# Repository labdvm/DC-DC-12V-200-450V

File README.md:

# DC-DC-12V-200-450V
DC-DC Buck convertor up to 70W@450V
This is modified DC-DC convertor from chinese product from Aliexpress with little enhancement.
Take out the transformer from original PCB and place to this PCB !
V1.3
Z32IT

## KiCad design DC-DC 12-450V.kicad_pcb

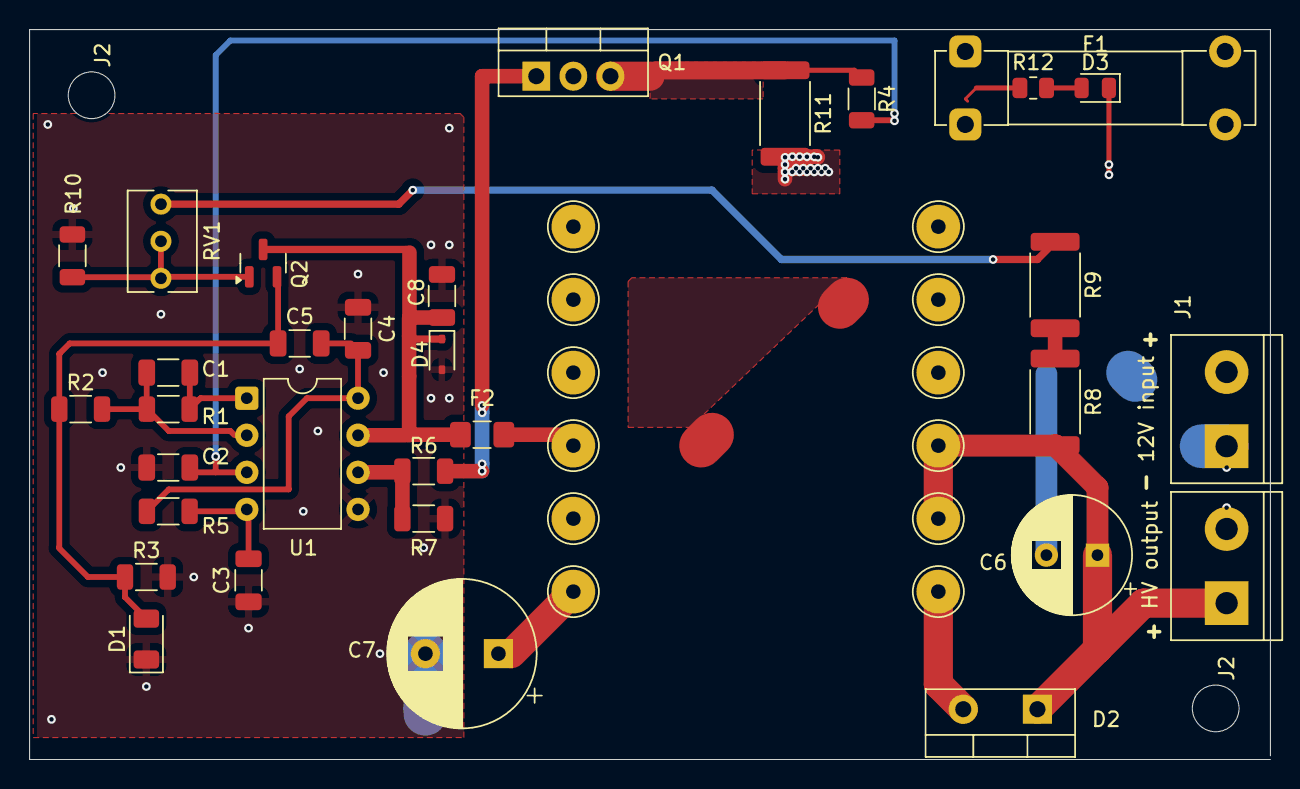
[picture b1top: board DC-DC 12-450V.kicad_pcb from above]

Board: 2 copper layers, 85.0 x 50.0 mm, 44 parts (0 on the bottom side), 19 nets.

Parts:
C1, C8: 100n; C_1206_3216Metric
C2, C4, C5: 10n; C_1206_3216Metric
C3: 3n3; C_1206_3216Metric
C6: 10u/450V; CP_Radial_D8.0mm_P3.50mm
C7: 1500u/16V; CP_Radial_D10.0mm_P5.00mm
D1: Green; LED_1206_3216Metric
D2: MUR860; TO-220-2_Vertical
D3: Amber; LED_0805_2012Metric
D4: PESD12VL1BA; D_SOD-323
F1: Fuse; Fuseholder_Clip-5x20mm_Bel_FC-203-22_Lateral_P17.80x5.00mm_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
F2: 1.5A/13.2V; Fuse_1206_3216Metric_Pad1.42x1.75mm_HandSolder
J1: 12V input; TerminalBlock_bornier-2_P5.08mm
J2: HV output; TerminalBlock_bornier-2_P5.08mm
PAD1, PAD6, PAD7: +12V; TestPoint_THTPad_D3.0mm_Drill1.5mm
PAD2, PAD3, PAD5, PAD8, PAD10, PAD11: e; TestPoint_THTPad_D3.0mm_Drill1.5mm
PAD4, PAD9: TestPoint_THTPad_D3.0mm_Drill1.5mm
PAD12: Q1-D; TestPoint_THTPad_D3.0mm_Drill1.5mm
Q1: IRF3205; TO-220-3_Vertical
Q2: S8050; SOT-23
R1: 100K; R_1206_3216Metric
R2, R3: 1K; R_1206_3216Metric
R4: 150R; R_1206_3216Metric
R5, R7: 5K1; R_1206_3216Metric
R6: 20R; R_1206_3216Metric
R8, R9: 240K/1W; R_2512_6332Metric
R10: 3K; R_1206_3216Metric
R11: 0.015R/3W; R_2512_6332Metric
R12: 1K; R_0805_2012Metric
RV1: 5K; Potentiometer_Bourns_3266Y_Vertical
U1: UC3843BN_DIP8; DIP-8_W7.62mm

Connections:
+12V: C7.1, F1.1, F2.1, PAD1.1, PAD2.2, PAD3.3, PAD7.7, PAD8.8, R12.2
/Q1-S: Q1.3 (S), R4.2, R11.1
/VCC: C8.1, D4.1 (A1), F2.2, Q2.3 (C), U1.7 (VCC)
GND: C2.2, C3.1, C4.2, C6.2, C7.2, C8.2, D1.1 (K), D3.1 (K), D4.2 (A2), J1.1, J2.2, R3.2, R7.2, R10.2, R11.2, U1.5 (GND)
unnamed: C5.1, D1.2 (A), Q2.2 (E), R2.1, R3.1
unnamed: C6.1, D2.1 (K), J2.1, PAD10.10, PAD11.11, R8.2
unnamed: D3.2 (A), R12.1
unnamed: F1.2, J1.2
unnamed: PAD5.5, PAD6.6
unnamed: Q1.1 (G), R6.1
unnamed: R8.1, R9.2
unnamed: R9.1, RV1.1
unnamed: R10.1, RV1.2, RV1.3
unnamed: C1.1, R1.2, U1.1 (COMP)
unnamed: C2.1, R4.1, U1.3 (CS)
unnamed: C1.2, R1.1, R2.2, U1.2 (FB)
unnamed: R6.2, R7.1, U1.6 (OUT)
unnamed: C3.2, R5.2, U1.4 (RC)
unnamed: C4.1, C5.2, R5.1, U1.8 (VREF)

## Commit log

2026-01-24 Enhance README with product modifications and version
    Added additional information about the modifications and version.
